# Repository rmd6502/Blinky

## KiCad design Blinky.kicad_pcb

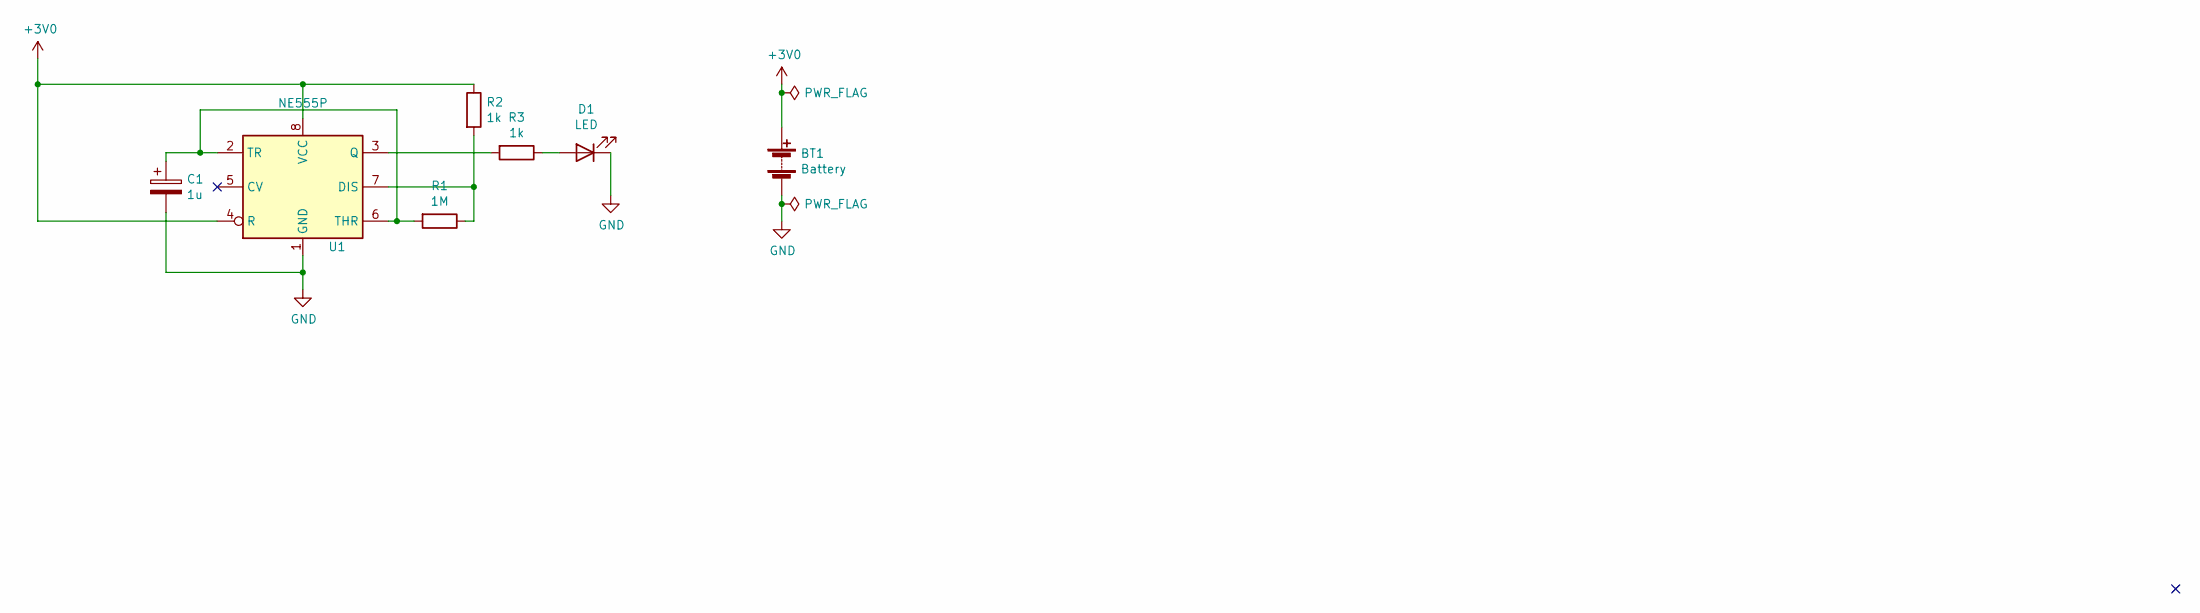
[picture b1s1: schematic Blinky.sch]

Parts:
BT1: Battery; BatteryHolder_Keystone_2462_2xAA
C1: 1u; CP_Radial_D4.0mm_P2.00mm
D1: LED; LED_D3.0mm
R1: 1M; R_Axial_DIN0204_L3.6mm_D1.6mm_P5.08mm_Horizontal
R2, R3: 1k; R_Axial_DIN0204_L3.6mm_D1.6mm_P5.08mm_Horizontal
U1: NE555P; DIP-8_W7.62mm

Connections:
+3V0: BT1.1 (+), R2.1, U1.4 (R), U1.8 (VCC)
GND: BT1.2 (-), C1.2, D1.1 (K), U1.1 (GND)
unnamed: C1.1, R1.2, U1.2 (TR), U1.6 (THR)
unnamed: D1.2 (A), R3.1
unnamed: R1.1, R2.2, U1.7 (DIS)
unnamed: R3.2, U1.3 (Q)

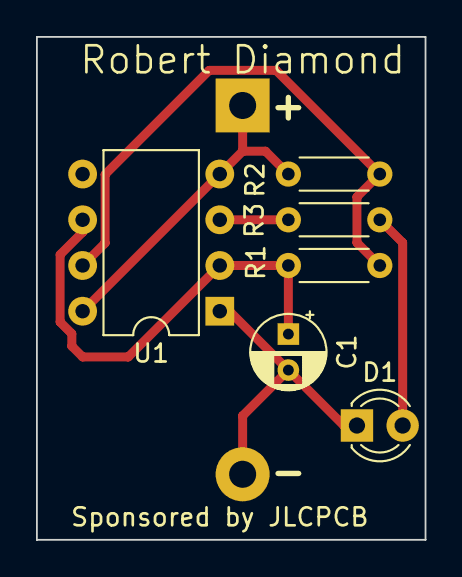
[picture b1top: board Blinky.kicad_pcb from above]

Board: 2 copper layers, 21.6 x 27.9 mm, 7 parts (1 on the bottom side), 6 nets.

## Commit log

2021-11-19 initial schematic
